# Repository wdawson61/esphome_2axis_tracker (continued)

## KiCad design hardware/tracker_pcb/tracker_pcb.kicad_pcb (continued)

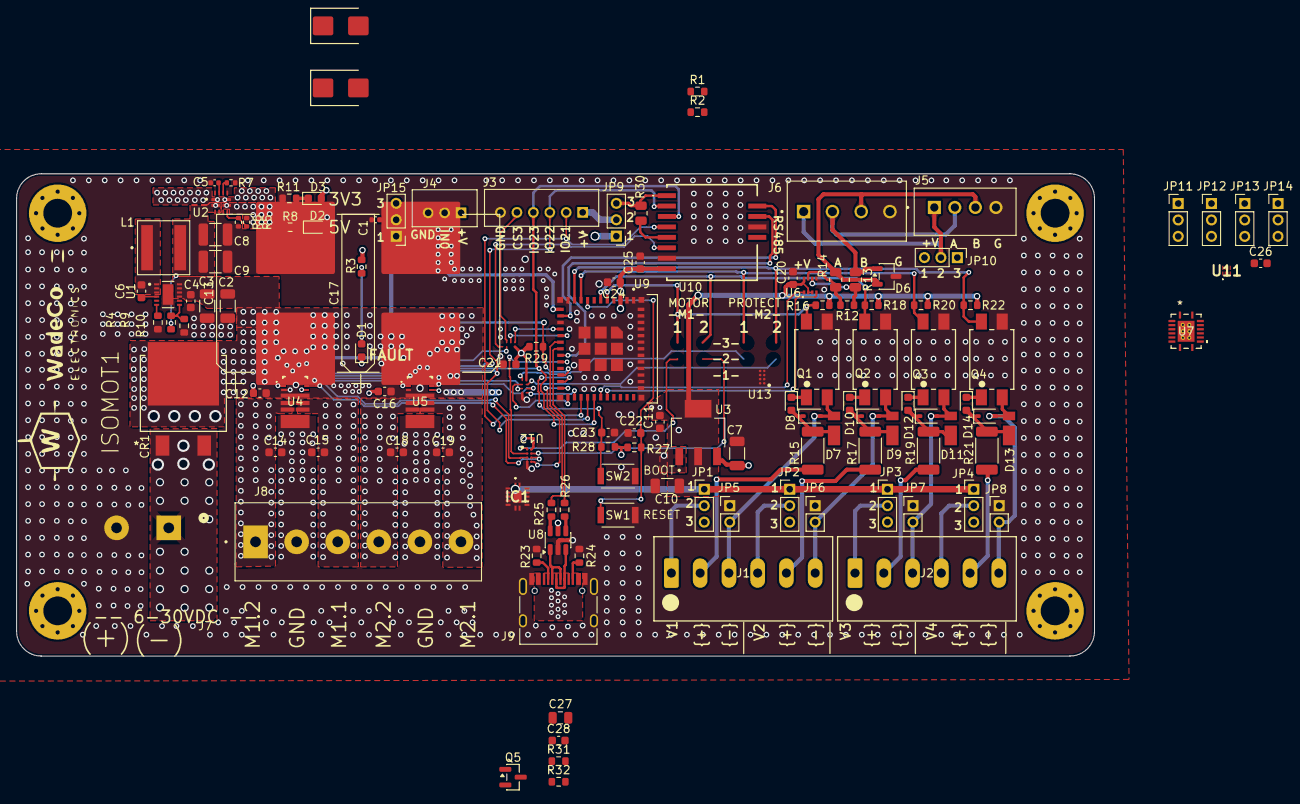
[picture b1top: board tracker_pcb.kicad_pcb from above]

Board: 4 copper layers, 131.2 x 58.7 mm, 129 parts (0 on the bottom side), 96 nets.

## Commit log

2025-11-10 Initial plan
2025-11-10 Add complete ESPHome firmware for 2-axis solar tracker with WIT-Motion HWT905
2025-11-10 Add comprehensive documentation: Quick Start Guide and Wiring Diagrams
2025-11-10 Update .gitignore and add implementation summary documentation
2025-11-12 Add actual wind sensor to tracker automatoin
2025-11-24 Adding ha-add-on branch
2025-12-08 Add libs and schematic and planning docs
2025-12-08 Add correct files
2025-12-08 Parts is parts
2025-12-10 Adding DRV8244
2025-12-10 Adding 8244 models
2025-12-11 Adding motor caps
2025-12-12 Routing begins
2025-12-12 More layout
2025-12-15 Hierarcical sheets
2025-12-17 More layout - adding rs485 an dinputmsheets
2025-12-18 add opto input module
2025-12-18 Work
2025-12-20 WIP it so good
2025-12-24 Complete but optos are using 5v pullups instead of 3v3. No bueno
2025-12-25 Added graphics to libs
    update .ignore
2025-12-26 experiment with esp32 module variant
2026-01-05 Including LORA wio-sx1262
2026-01-05 update text
2026-01-09 VIA changes
2026-01-10 add diode to libs
2026-01-15 Add jst xh for inputs
2026-01-15 Add "hardware interlock" option to use iso ins 1-4 as hardware interlock for HBRDIGE PWM signals
2026-01-20 ss changes
2026-01-20 Add fuseholder
2026-01-26 Changed to phenix screw terminal connectors
2026-01-27 Dual rs485 connectors
2026-01-27 WIPs
2026-01-30 Adjust ss
2026-02-02 Beef up 5v supply and add new power mux
2026-02-03 Modify iso circuit for best CTR
2026-02-04 Add zener diodes to properly bias optos across 6-35V input rnge
2026-02-19 add 3pin jst for analog
2026-03-23 update BOM
2026-03-23 Update optoisolator pin designator SS
    # Conflicts:
    # hardware/tracker_pcb/tracker_pcb.kicad_pcb
2026-05-06 v2 hardware changes
2026-05-28 more motor safety
2026-05-29 Motor safety edits
